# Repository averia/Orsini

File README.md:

Orsini
======

An atmel328p-pu with Midi in-thru-out, 6 potentiometers and a DAC out.
The six potentiometers have a minijack switch that can be controlled by CV.

Videos David Ghosting
- [Video 1](https://youtu.be/K4ag43L7bm8)

Arduino sketches

- [MidiVox](https://github.com/averia/Orsini/tree/master/software/MidiVox_Orsini)
   scketch adapted from Narbotic Midivox
- [ORSINI_ARPEGGIO](https://github.com/averia/Orsini/tree/master/software/ORSINI_ARPEGGIO)

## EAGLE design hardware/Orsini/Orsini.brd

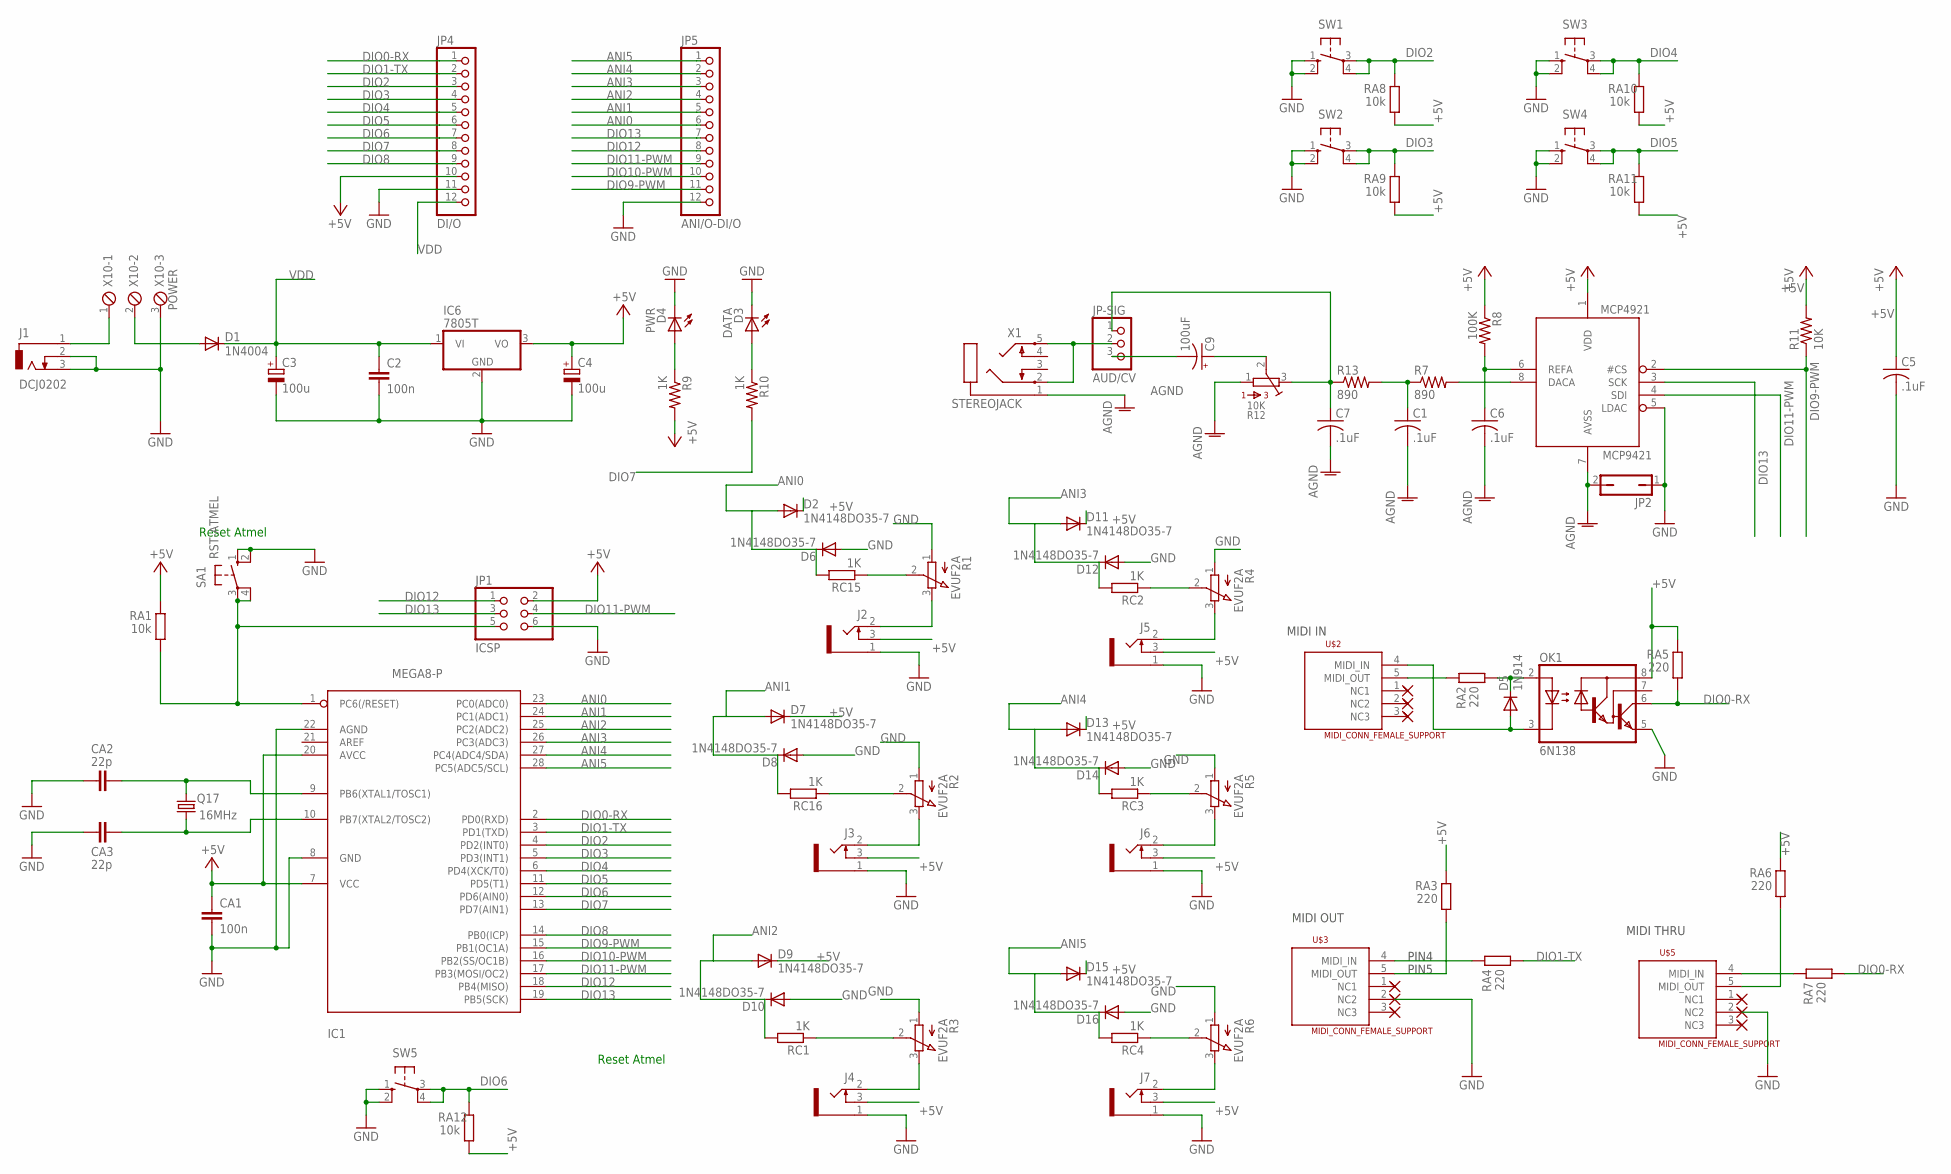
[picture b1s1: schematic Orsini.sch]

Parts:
C1, C7: .1uF; C050-025X075
C2: 100n; C050-025X075
C3, C4: 100u; E2,5-7
C5, C6: .1uF; C025-025X050
C9: 100uF; E2,5-5
CA1: 100n; C050-025X075
CA2, CA3: 22p; C050-025X075
D1: 1N4004; DO41-10
D2, D6, D7, D8, D9, D10, D11, D12, D13, D14, D15, D16: 1N4148DO35-7; DO35-7
D3: DATA; LED4MM
D4: PWR; LED4MM
D5: 1N914; DO34-7
IC1: MEGA8-P; DIL28-3
IC6: 7805T; TO220H
J1: DCJ0202
J2, J3, J4, J5, J6, J7: 1502_03SLOTTED; 1502_03_SLOTTED
JP1: ICSP; 2X03
JP2: JP1Q; JP1
JP4: DI/O; 1X12
JP5: ANI/O-DI/O; 1X12
JP-SIG: AUD/CV; 1X03
MCP4921: MCP9421; DIL08
OK1: 6N138; DIL08
Q17: 16MHz; HC49/S
R1, R2, R3, R4, R5, R6: EVUF2A; EVUF
R7, R13: 890; 0207/7
R8: 100K; 0207/7
R9, R10: 1K; 0207/7
R11: 10K; 0207/10
R12: 10K; 3386F
RA1, RA8, RA9, RA10, RA11, RA12: 10k; 0207/10
RA2, RA3, RA4, RA5, RA6, RA7: 220; 0207/10
RC1, RC2, RC3, RC4, RC15, RC16: 1K; 0207/10
SA1: RST-ATMEL; B3F-10XX
SW1, SW2, SW3, SW4, SW5: 40-XX; B3F-40XX
U$2, U$3, U$5: MIDI_CONN_FEMALE_SUPPORT; DIN_5_FEMALE_SUPPORT
X1: STEREOJACK; STX3001
X10: POWER; 3POL254

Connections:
56: D5.C, OK1.2 (A), RA2.2
1235: RA3.2, U$3.5 (MIDI_OUT)
+5V: C4.+, C5.1, CA1.1, D2.C, D7.C, D9.C, D11.C, D13.C, D15.C, IC1.7 (VCC), IC1.20 (AVCC), IC6.3 (VO), J2.3, J3.3, J4.3, J5.3, J6.3, J7.3, JP1.2, JP4.10, MCP4921.1 (VDD), OK1.8 (VCC), R8.1, R9.2, R11.2, RA1.1, RA3.1, RA5.1, RA6.1, RA8.2, RA9.2, RA10.2, RA11.2, RA12.2
AGND: C1.2, C6.2, C7.2, JP2.2, MCP4921.7 (AVSS), R12.1, X1.1
ANI0: D2.A, D6.C, IC1.23 (PC0(ADC0)), JP5.6, RC15.2
ANI1: D7.A, D8.C, IC1.24 (PC1(ADC1)), JP5.5, RC16.2
ANI2: D9.A, D10.C, IC1.25 (PC2(ADC2)), JP5.4, RC1.2
ANI3: D11.A, D12.C, IC1.26 (PC3(ADC3)), JP5.3, RC2.2
ANI4: D13.A, D14.C, IC1.27 (PC4(ADC4/SDA)), JP5.2, RC3.2
ANI5: D15.A, D16.C, IC1.28 (PC5(ADC5/SCL)), JP5.1, RC4.2
DIO0-RX: IC1.2 (PD0(RXD)), JP4.1, OK1.6 (VO), RA5.2, RA7.2
DIO1-TX: IC1.3 (PD1(TXD)), JP4.2, RA4.2
DIO2: IC1.4 (PD2(INT0)), JP4.3, RA8.1, SW1.3, SW1.4 (P1)
DIO3: IC1.5 (PD3(INT1)), JP4.4, RA9.1, SW2.3, SW2.4 (P1)
DIO4: IC1.6 (PD4(XCK/T0)), JP4.5, RA10.1, SW3.3, SW3.4 (P1)
DIO5: IC1.11 (PD5(T1)), JP4.6, RA11.1, SW4.3, SW4.4 (P1)
DIO6: IC1.12 (PD6(AIN0)), JP4.7, RA12.1, SW5.3, SW5.4 (P1)
DIO7: IC1.13 (PD7(AIN1)), JP4.8, R10.2
DIO8: IC1.14 (PB0(ICP)), JP4.9
DIO9-PWM: IC1.15 (PB1(OC1A)), JP5.11, MCP4921.2 (#CS), R11.1
DIO10-PWM: IC1.16 (PB2(SS/OC1B)), JP5.10
DIO11-PWM: IC1.17 (PB3(MOSI/OC2)), JP1.4, JP5.9, MCP4921.4 (SDI)
DIO12: IC1.18 (PB4(MISO)), JP1.1, JP5.8
DIO13: IC1.19 (PB5(SCK)), JP1.3, JP5.7, MCP4921.3 (SCK)
GND: C2.2, C3.-, C4.-, C5.2, CA1.2, CA2.2, CA3.2, D3.A (C), D4.A (C), D6.A, D8.A, D10.A, D12.A, D14.A, D16.A, IC1.8 (GND), IC1.22 (AGND), IC6.2 (GND), J1.2, J1.3, J2.1, J3.1, J4.1, J5.1, J6.1, J7.1, JP1.6, JP2.1, JP4.11, JP5.12, MCP4921.5 (LDAC), OK1.5 (GND), R1.1 (A), R2.1 (A), R3.1 (A), R4.1 (A), R5.1 (A), R6.1 (A), SA1.1 (S), SA1.2 (S1), SW1.1 (S), SW1.2 (S1), SW2.1 (S), SW2.2 (S1), SW3.1 (S), SW3.2 (S1), SW4.1 (S), SW4.2 (S1), SW5.1 (S), SW5.2 (S1), U$3.2 (NC2), U$5.2 (NC2), X10.3
unnamed: J1.1, X10.1
unnamed: IC1.1 (PC6(/RESET)), JP1.5, RA1.2, SA1.3, SA1.4 (P1)
unnamed: R1.2 (S), RC15.1
unnamed: D1.A, X10.2
unnamed: CA2.1, IC1.9 (PB6(XTAL1/TOSC1)), Q17.2
unnamed: CA3.1, IC1.10 (PB7(XTAL2/TOSC2)), Q17.1
unnamed: J2.2, R1.3 (E)
unnamed: RA4.1, U$3.4 (MIDI_IN)
unnamed: RA6.2, U$5.5 (MIDI_OUT)
unnamed: R2.2 (S), RC16.1
unnamed: J3.2, R2.3 (E)
unnamed: R3.2 (S), RC1.1
unnamed: RA7.1, U$5.4 (MIDI_IN)
unnamed: RA2.1, U$2.5 (MIDI_OUT)
unnamed: MCP4921.8 (DACA), R7.2
unnamed: JP-SIG.2, X1.2, X1.5
unnamed: C7.1, JP-SIG.1, R12.3, R13.1
unnamed: C6.1, MCP4921.6 (REFA), R8.2
unnamed: C1.1, R7.1, R13.2
unnamed: C9.-, JP-SIG.3
unnamed: D3.K (A), R10.1
unnamed: J4.2, R3.3 (E)
unnamed: R4.2 (S), RC2.1
unnamed: R5.2 (S), RC3.1
unnamed: D4.K (A), R9.1
unnamed: J5.2, R4.3 (E)
unnamed: J6.2, R5.3 (E)
unnamed: J7.2, R6.3 (E)
unnamed: R6.2 (S), RC4.1
unnamed: C9.+, R12.2
PIN5: D5.A, OK1.3 (C), U$2.4 (MIDI_IN)
VDD: C2.1, C3.+, D1.C, IC6.1 (VI), JP4.12

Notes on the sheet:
Reset Atmel
PIN4
PIN5
MIDI IN
MIDI OUT
MIDI THRU

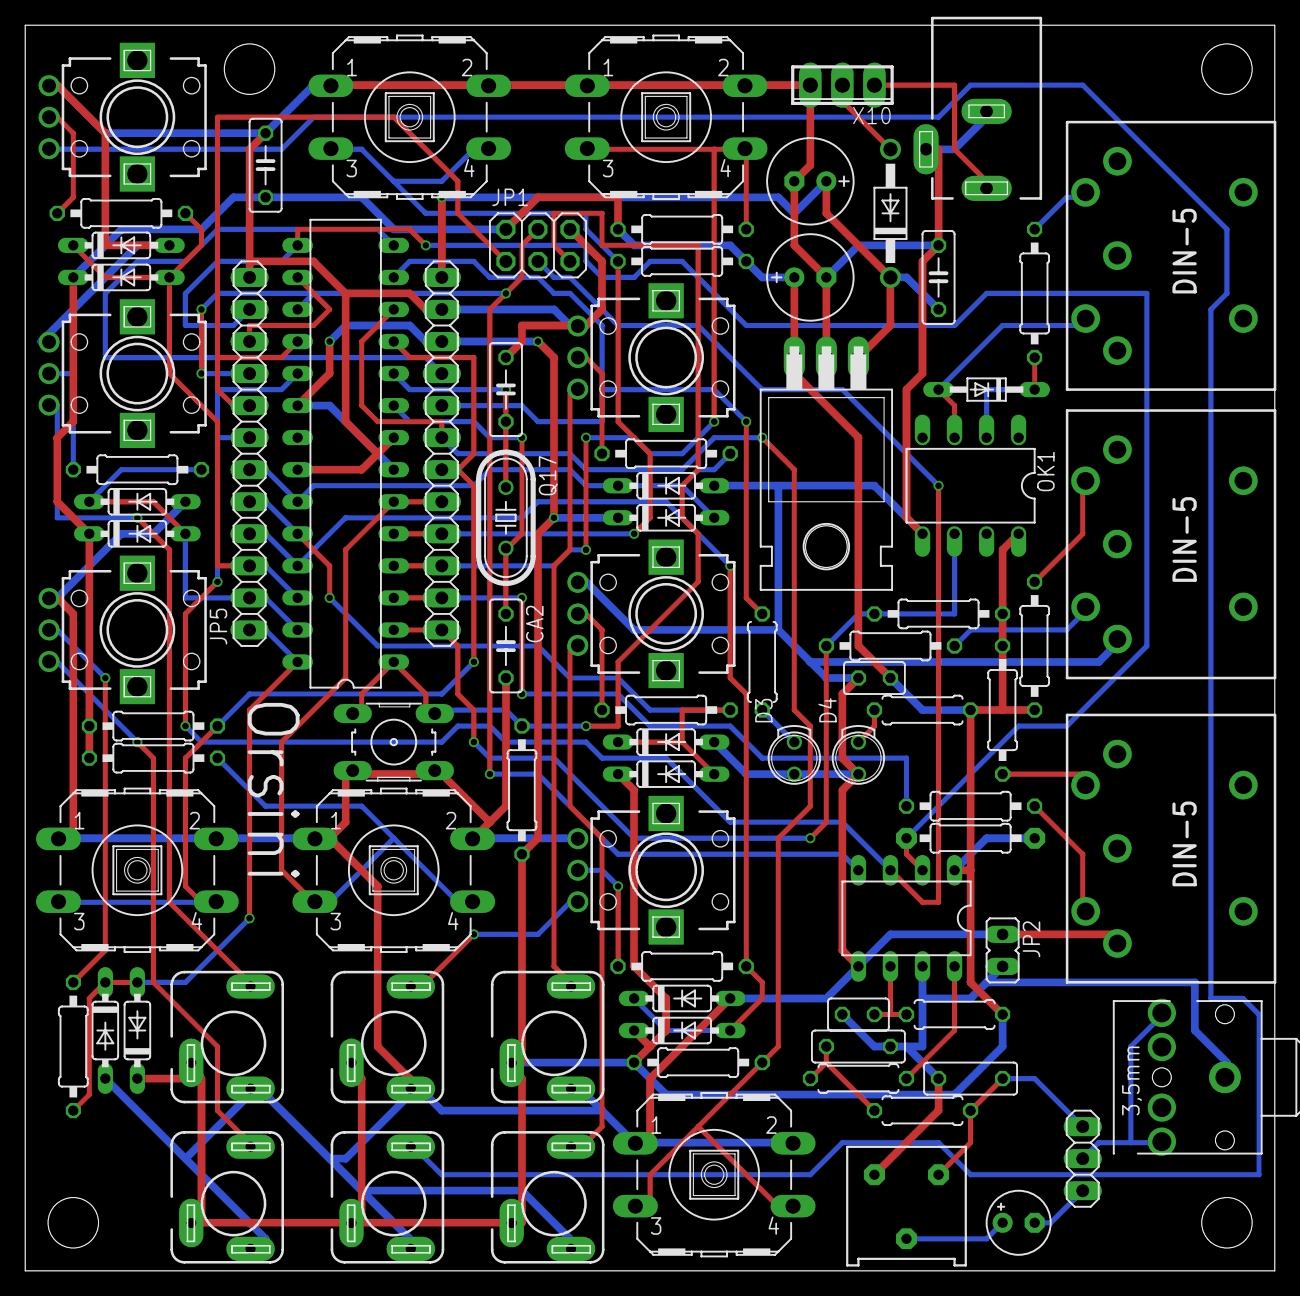
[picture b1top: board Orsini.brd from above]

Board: 4 copper layers, 99.0 x 98.7 mm, 86 parts (0 on the bottom side), 57 nets.

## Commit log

2015-07-18 Create MidiVox_Orsini
2015-07-18 MidiVox_Orsini
2015-07-19 Merge branch 'master' of https://github.com/averia/Orsini
    # Please enter a commit message to explain why this merge is necessary,
    # especially if it merges an updated upstream into a topic branch.
    #
    # Lines starting with '#' will be ignored, and an empty message aborts
    # the commit.
2023-06-23 Update README.md
    .
